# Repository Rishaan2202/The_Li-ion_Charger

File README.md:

# The_Li-ion_Charger
<br>
<br>

<h2> This is a basic single Li-ion battery Charger, which has a Type-C Input and a TP4056 Charger, I'm Kinda speedrunning this thing rn!!! </h2>
<br>
<br>

<h2> Here's the Schematic: </h2>
<br>

<br>
<br>

<h2> PCB!: </h2>
<br>

<br>
<br>

<h2> Now it's time for the 3D model!: </h2>
<br>

<br>
<br>

<h2> So here are the cart SSs for the PCB + components: </h2>
<br>

<br>
<br>

<br>
<br>

<h2> Total Cost: ~$25 </h2>
<br>
<br>

<h2> This is enough ig! </h2>
<br>
<br>

<h2> TYSM!!! </h2>

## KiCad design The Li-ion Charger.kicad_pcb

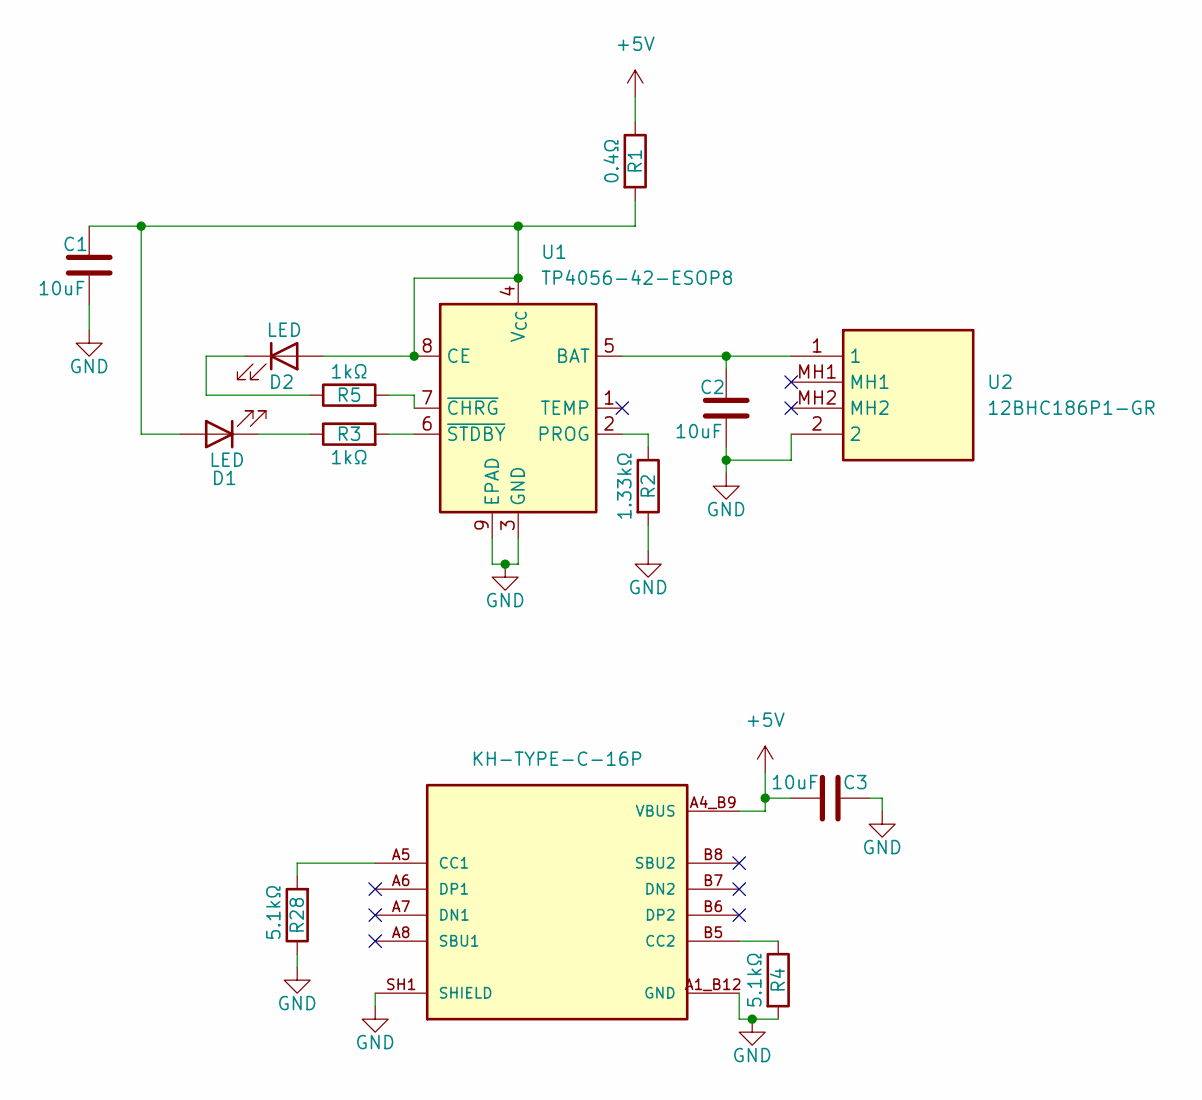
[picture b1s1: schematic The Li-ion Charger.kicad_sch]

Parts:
C1, C2, C3: 10uF; C_0805_2012Metric
D1, D2: LED; LED_0603_1608Metric
J6: KH-TYPE-C-16P; KINGHELM_KH-TYPE-C-16P; PARTREV A0
R1: 0.4Ω; R_0805_2012Metric
R2: 1.33kΩ; R_0805_2012Metric
R3, R5: 1kΩ; R_0805_2012Metric
R4, R28: 5.1kΩ; R_0805_2012Metric
U1: TP4056-42-ESOP8; SOIC-8-1EP_3.9x4.9mm_P1.27mm_EP2.41x3.3mm_ThermalVias
U2: 12BHC186P1-GR; 12BHC186P1GR; Mouser Part Number 12BHC186P1-GR

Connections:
+5V: C3.1, J6.A4_B9 (VBUS), J6.A9_B4 (VBUS), R1.1
GND: C1.1, C2.1, C3.2, J6.A1_B12 (GND), J6.A12_B1 (GND), J6.SH1 (SHIELD), J6.SH2 (SHIELD), J6.SH3 (SHIELD), J6.SH4 (SHIELD), R2.2, R4.2, R28.1, U1.3 (GND), U1.9 (EPAD), U2.2
unnamed: C1.2, D1.2 (A), D2.2 (A), R1.2, U1.4 (V_{CC}), U1.8 (CE)
unnamed: D1.1 (K), R3.1
unnamed: D2.1 (K), R5.1
unnamed: J6.A5 (CC1), R28.2
unnamed: J6.B5 (CC2), R4.1
unnamed: C2.2, U1.5 (BAT), U2.1
unnamed: R2.1, U1.2 (PROG)
unnamed: R5.2, U1.7 (~CHRG)
unnamed: R3.2, U1.6 (~STDBY)

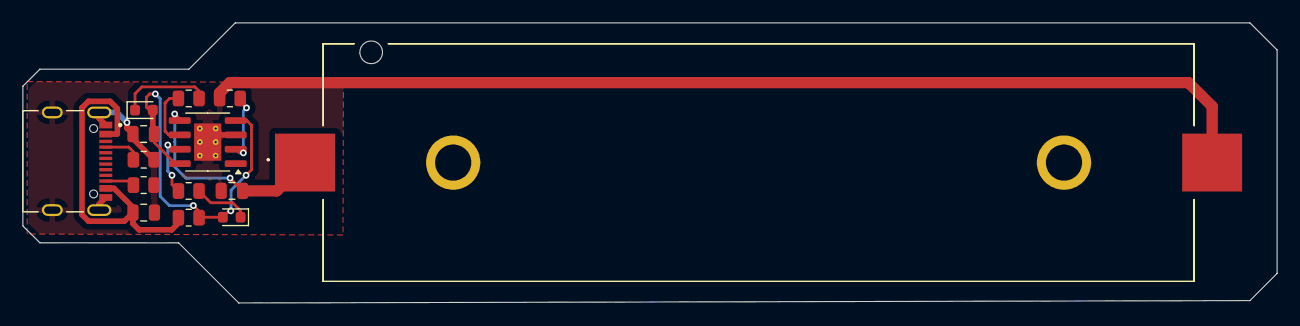
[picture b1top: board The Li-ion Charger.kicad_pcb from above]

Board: 2 copper layers, 110.9 x 24.8 mm, 14 parts (0 on the bottom side), 11 nets.

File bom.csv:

Designator,Footprint,Quantity,Value,Li-Ion Circuits,Robu.in
"C1, C2, C3",805,3,10uF,Done,
"D1, D2",603,2,LED,Done,
J6,KINGHELM_KH-TYPE-C-16P,1,KH-TYPE-C-16P,,Done
R1,805,1,0.4Ω,Done,
R2,805,1,1.33kΩ,Done,
"R28, R4",805,2,5.1kΩ,Done,
"R3, R5",805,2,1kΩ,Done,
U1,SOIC-8-1EP_3.9x4.9mm_P1.27mm_EP2.41x3.3mm_ThermalVias,1,TP4056-42-ESOP8,,Done
U2,12BHC186P1GR,1,12BHC186P1-GR,,Done

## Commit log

2025-12-12 Update README with PCB component images and costs
    Added images and cost details for PCB components.
2025-12-23 Create PCB
